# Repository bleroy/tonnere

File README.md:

## Project Tonnere

The EclaireXL was a partially open Atari XL FPGA implementation designed almost a decade ago. This project is intended to be a fully open community follow up version.

## Status

For now there is only a hardware design from which a physical board has been produced. The design goals of this are described below.

## Memory

3 independent banks of RAM from FPGA

- 512KB 16-bit wide 10ns SRAM (for VBXE)
- 2048KB 16-bit wide 10ns SRAM (primary Atari core)
- 32MB 16-bit wide SDRAM (secondary Atari core etc - for large memory expansions, cartridge emulation etc)

## Video output

- HDMI driven directly by FPGA
- Analog video driven by FPGA (3 pins/channel - ~8-bit/channel resolution) filtered/buffered by THS7316.
- NTSC in 480i or 480p, PAL in 576i or 576p
- Polyphasic and area-based scaler allowing 720p, 1080i etc

## Audio output

- PCM5102A DAC

## Audio input

- 12-bit ADC for PBI, SIO, 3.5mm left/right on STM microcontroller

## Joystick ports 1-4

- Directly connected to FPGA (via level shifters)
- Paddle support using STM ADC inputs

## Six USB ports

- 1 USB A internal for keyboard
- 3 USB A external for joystick, keyboard etc
- 1 USB C for power only (next to power switch)
- 1 rear USB C for STM32 DFU (to program it), or to be a mass-storage slave to a PC to copy data on.

## Atari peripheral emulator (ESP32 microcontroller/almost Fujinet)

- Wifi support
- Serial connection to STM32
- SPI master to FPGA (for DMA to RAM, faster than serial via STM)
- SIO pins (all)
- Audio out DAC goes to SIO audio in
- Slave to STM32
- Slave to Atari via SIO
- JTAG for debugging

## Firmware/control (STM32)

- SPI master to FPGA SPI flash chip (to program)
- Can restart FPGA
- SRAM port connected to FPGA (for DMA to Atari core RAM + RAM banks)
- IRQ from FPGA
- 4-bit external SD card interface
- SPI to internal micro SD card (will appear as IDE hard drive to Atari core)
- ADC for sampling (see audio in)
- Serial connection for communication for Atari peripheral emulator
- USB port + stack
- DFU mode for programming, can then program FPGA flash and ESP32 via serial (+BOOT etc).
- HDMI i2c link (to get mode support)
- PLL i2c link (6 programmable clocks for FPGA)
- SWD port for debugging
- UART port for debugging/expansion
- Will run menus etc, via DMA to Atari core (+ potentially framebuffer)

## Atari core (Cyclone 10 LP FPGA)

- Core Atari XL and Atari 800 support
- 2x/4x colour clock Antic/GTIA support
- VBXE
- PokeyMAX
- HDD via IDE emulation on microsd
- Turbo freezer
- Common cartridge banking logic (on RAM)

## Atari ports

- Left cartridge
- PBI with standard extensions (enabled/selected via jumper), 50 pin edge and 50 pin header option.
- SIO (with motor control, without 12V)
- Start/select/option/reset switch headers
- 4 joystick ports

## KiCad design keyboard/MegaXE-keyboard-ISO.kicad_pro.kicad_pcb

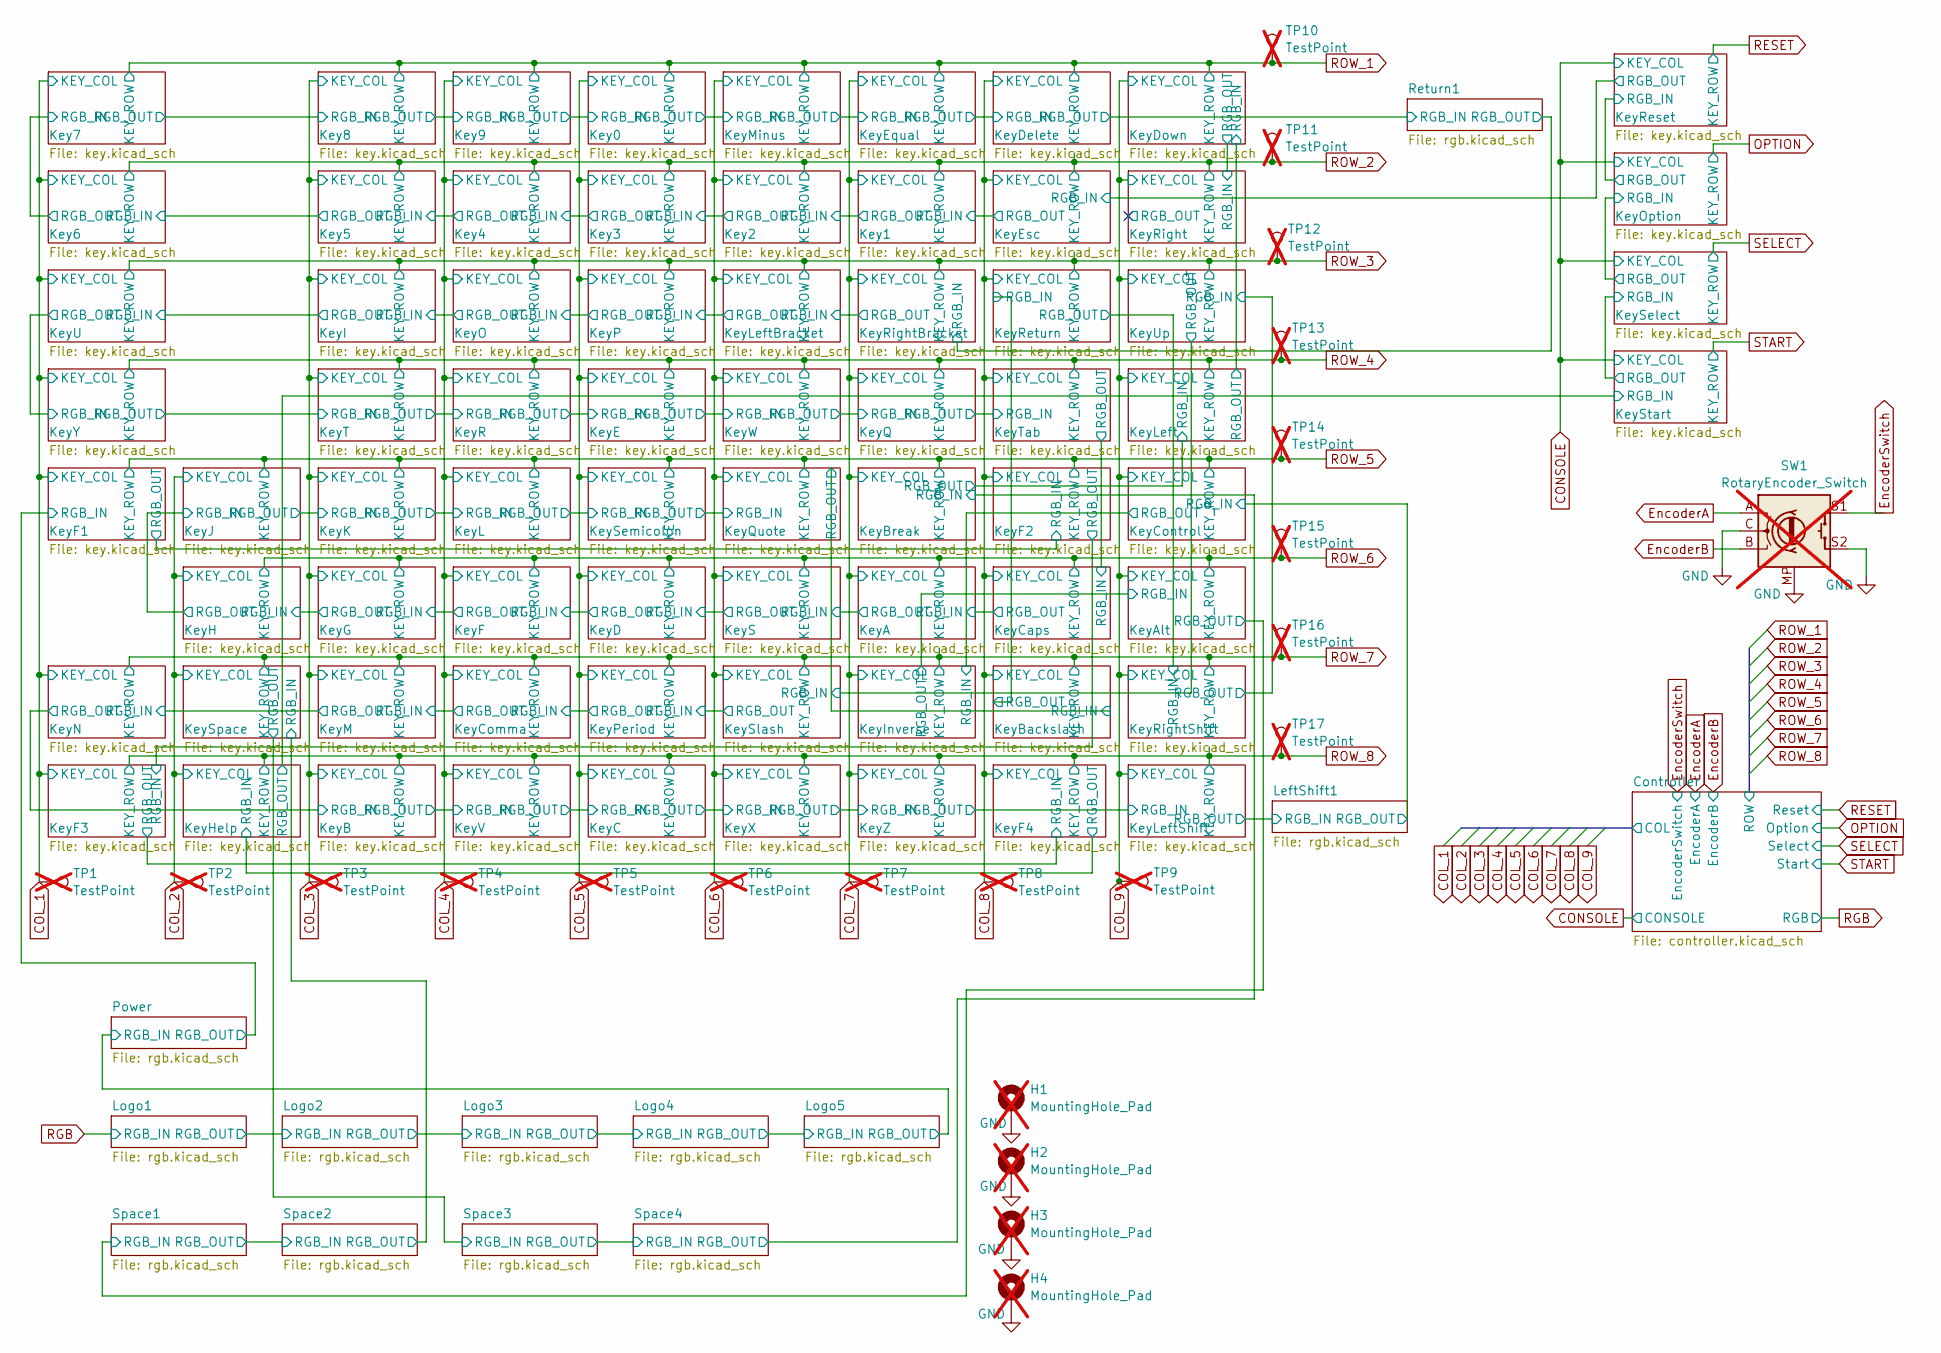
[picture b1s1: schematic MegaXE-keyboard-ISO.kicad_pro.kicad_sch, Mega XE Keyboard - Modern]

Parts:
H1, H2, H3, H4: MountingHole_Pad; MountingHole_2.2mm_M2_Pad_Via; not fitted
SW1: RotaryEncoder_Switch; RotaryEncoder_Alps_EC11E-Switch_Vertical_H20mm; LCSC Part # C470748; not fitted
TP1, TP2, TP3, TP4, TP5, TP6, TP7, TP8, TP9, TP10, TP11, TP12, TP13, TP14, TP15, TP16, TP17: TestPoint; TestPoint_THTPad_D1.0mm_Drill0.5mm; not fitted

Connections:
COL_1: TP1.1 (1_1); also elsewhere on the board
COL_2: TP2.1 (1_1); also elsewhere on the board
COL_3: TP3.1 (1_1); also elsewhere on the board
COL_4: TP4.1 (1_1); also elsewhere on the board
COL_5: TP5.1 (1_1); also elsewhere on the board
COL_6: TP6.1 (1_1); also elsewhere on the board
COL_7: TP7.1 (1_1); also elsewhere on the board
COL_8: TP8.1 (1_1); also elsewhere on the board
COL_9: TP9.1 (1_1); also elsewhere on the board
EncoderA: SW1.A; also elsewhere on the board
EncoderB: SW1.B; also elsewhere on the board
EncoderSwitch: SW1.S1; also elsewhere on the board
GND: H1.1 (1_1), H2.1 (1_1), H3.1 (1_1), H4.1 (1_1), SW1.C, SW1.MP, SW1.S2; also elsewhere on the board
ROW_1: TP10.1 (1_1); also elsewhere on the board
ROW_2: TP11.1 (1_1); also elsewhere on the board
ROW_3: TP12.1 (1_1); also elsewhere on the board
ROW_4: TP13.1 (1_1); also elsewhere on the board
ROW_5: TP14.1 (1_1); also elsewhere on the board
ROW_6: TP15.1 (1_1); also elsewhere on the board
ROW_7: TP16.1 (1_1); also elsewhere on the board
ROW_8: TP17.1 (1_1); also elsewhere on the board

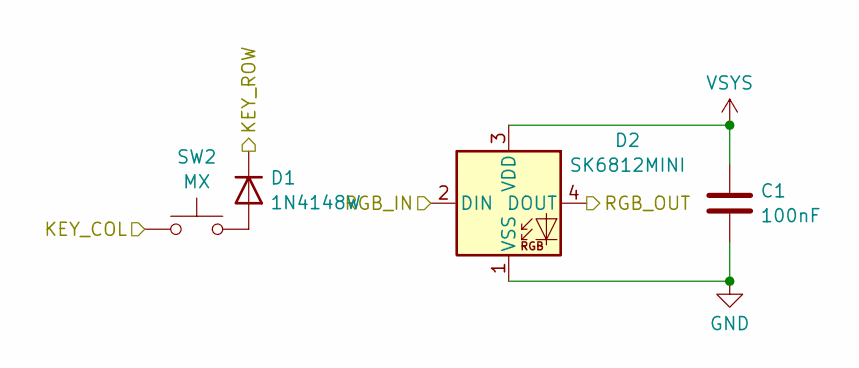
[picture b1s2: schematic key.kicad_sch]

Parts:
C1: 100nF; C_0402_1005Metric; JLCPCB Part # C1525
D1: 1N4148W; D_SOD-123; JLCPCB Part # C81598
D2: SK6812MINI; LED_SK6812MINI-E_3.2x2.8mm_P1.5mm_ReverseMount; JLCPCB Part # C5378731
SW2: MX; Kailh_socket_MX_1-00U; JLCPCB Part # C41430893

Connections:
/Key6/RGB_OUT: D2.2 (DIN); also elsewhere on the board
/Key7/RGB_OUT: D2.4 (DOUT); also elsewhere on the board
COL_1: SW2.1; also elsewhere on the board
GND: C1.2, D2.1 (VSS); also elsewhere on the board
unnamed: D1.2 (A), SW2.2
ROW_1: D1.1 (K); also elsewhere on the board
VSYS: C1.1, D2.3 (VDD); also elsewhere on the board

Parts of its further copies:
C2, C3, C4, C5, C6, C7, C8, C9, C10, C11, C12, C13, C14, C15, C16, C17, C18, C19, C20, C21, C22, C23, C24, C25, C26, C27, C28, C29, C30, C31, C32, C33, C34, C35, C36, C37, C38, C39, C40, C41, C42, C43, C44, C45, C46, C47, C48, C49, C50, C51, C52, C53, C54, C55, C56, C57, C58, C59, C60, C61, C62, C63, C64, C65, C66, C95, C96, C97, C98, C99: 100nF; C_0402_1005Metric; JLCPCB Part # C1525
D3, D5, D7, D9, D11, D13, D15, D17, D19, D21, D23, D25, D27, D29, D31, D33, D35, D37, D39, D41, D43, D45, D47, D49, D51, D53, D55, D57, D59, D61, D63, D65, D67, D69, D71, D73, D75, D77, D79, D81, D83, D85, D87, D89, D91, D93, D95, D97, D99, D101, D103, D105, D107, D109, D111, D113, D115, D117, D119, D121, D123, D125, D127, D129, D131, D144, D146, D148, D150, D152: 1N4148W; D_SOD-123; JLCPCB Part # C81598
D4, D6, D8, D10, D12, D14, D16, D18, D20, D22, D24, D26, D28, D30, D32, D34, D36, D38, D40, D42, D44, D46, D48, D50, D52, D54, D56, D58, D60, D62, D64, D66, D68, D70, D72, D74, D76, D78, D80, D82, D84, D86, D88, D90, D92, D94, D96, D98, D100, D102, D104, D106, D108, D110, D112, D114, D116, D118, D120, D122, D124, D126, D128, D130, D132, D145, D147, D149, D151, D153: SK6812MINI; LED_SK6812MINI-E_3.2x2.8mm_P1.5mm_ReverseMount; JLCPCB Part # C5378731
SW3, SW4, SW5, SW6, SW7, SW8, SW9, SW10, SW11, SW12, SW13, SW14, SW15, SW16, SW17, SW18, SW19, SW20, SW21, SW22, SW23, SW24, SW25, SW26, SW27, SW28, SW29, SW30, SW31, SW32, SW33, SW34, SW35, SW36, SW37, SW38, SW39, SW40, SW41, SW42, SW43, SW44, SW45, SW46, SW47, SW48, SW49, SW50, SW51, SW52, SW53, SW54, SW55, SW56, SW57, SW58, SW59, SW60, SW61, SW62, SW63, SW64, SW65, SW66, SW67, SW70, SW71, SW72, SW73, SW74: MX; Kailh_socket_MX_1-00U; JLCPCB Part # C41430893

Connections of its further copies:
/Key0/RGB_IN: D40.4 (DOUT), D58.2 (DIN)
/Key0/RGB_OUT: D58.4 (DOUT), D72.2 (DIN)
/Key1/RGB_IN: D88.2 (DIN), D104.4 (DOUT)
/Key1/RGB_OUT: D74.2 (DIN), D88.4 (DOUT)
/Key2/RGB_OUT: D56.2 (DIN), D74.4 (DOUT)
/Key3/RGB_OUT: D42.2 (DIN), D56.4 (DOUT)
/Key4/RGB_OUT: D36.2 (DIN), D42.4 (DOUT)
/Key5/RGB_OUT: D4.2 (DIN), D36.4 (DOUT)
/Key6/RGB_OUT: D4.4 (DOUT); also elsewhere on the board
/Key7/RGB_OUT: D38.2 (DIN); also elsewhere on the board
/Key8/RGB_OUT: D38.4 (DOUT), D40.2 (DIN)
/KeyA/RGB_IN: D96.2 (DIN), D106.4 (DOUT)
/KeyA/RGB_OUT: D78.2 (DIN), D96.4 (DOUT)
/KeyAlt/RGB_IN: D98.4 (DOUT), D149.2 (DIN)
/KeyAlt/RGB_OUT: D149.4 (DOUT); also elsewhere on the board
/KeyB/RGB_IN: D12.4 (DOUT), D24.2 (DIN)
/KeyB/RGB_OUT: D24.4 (DOUT), D54.2 (DIN)
/KeyBackslash/RGB_IN: D86.4 (DOUT), D153.2 (DIN)
/KeyBackslash/RGB_OUT: D108.2 (DIN), D153.4 (DOUT)
/KeyBreak/RGB_IN: D151.2 (DIN); also elsewhere on the board
/KeyBreak/RGB_OUT: D147.2 (DIN), D151.4 (DOUT)
/KeyC/RGB_IN: D54.4 (DOUT), D70.2 (DIN)
/KeyC/RGB_OUT: D70.4 (DOUT), D76.2 (DIN)
/KeyCaps/RGB_IN: D106.2 (DIN), D114.4 (DOUT)
/KeyComma/RGB_IN: D52.2 (DIN), D60.4 (DOUT)
/KeyComma/RGB_OUT: D26.2 (DIN), D52.4 (DOUT)
/KeyControl/RGB_IN: D112.2 (DIN); also elsewhere on the board
/KeyControl/RGB_OUT: D98.2 (DIN), D112.4 (DOUT)
/KeyD/RGB_IN: D64.2 (DIN), D78.4 (DOUT)
/KeyD/RGB_OUT: D50.2 (DIN), D64.4 (DOUT)
/KeyDelete/RGB_IN: D92.4 (DOUT), D110.2 (DIN)
/KeyDelete/RGB_OUT: D110.4 (DOUT); also elsewhere on the board
/KeyDown/RGB_IN: D122.2 (DIN), D147.4 (DOUT)
/KeyDown/RGB_OUT: D122.4 (DOUT), D145.2 (DIN)
/KeyE/RGB_IN: D46.4 (DOUT), D68.2 (DIN)
/KeyE/RGB_OUT: D68.4 (DOUT), D80.2 (DIN)
/KeyEqual/RGB_IN: D72.4 (DOUT), D92.2 (DIN)
/KeyEsc/RGB_IN: D104.2 (DIN), D124.4 (DOUT)
/KeyF1/RGB_IN: D10.2 (DIN); also elsewhere on the board
/KeyF1/RGB_OUT: D10.4 (DOUT), D116.2 (DIN)
/KeyF2/RGB_OUT: D20.2 (DIN), D116.4 (DOUT)
/KeyF3/RGB_OUT: D20.4 (DOUT), D118.2 (DIN)
/KeyF4/RGB_OUT: D22.2 (DIN), D118.4 (DOUT)
/KeyF/RGB_OUT: D28.2 (DIN), D50.4 (DOUT)
/KeyG/RGB_OUT: D16.2 (DIN), D28.4 (DOUT)
/KeyH/RGB_OUT: D14.2 (DIN), D16.4 (DOUT)
/KeyHelp/RGB_OUT: D22.4 (DOUT), D130.2 (DIN)
/KeyI/RGB_IN: D34.2 (DIN), D44.4 (DOUT)
/KeyI/RGB_OUT: D6.2 (DIN), D34.4 (DOUT)
/KeyJ/RGB_OUT: D14.4 (DOUT), D30.2 (DIN)
/KeyK/RGB_OUT: D30.4 (DOUT), D48.2 (DIN)
/KeyL/RGB_OUT: D48.4 (DOUT), D66.2 (DIN)
/KeyLeftBracket/RGB_IN: D82.2 (DIN), D90.4 (DOUT)
/KeyLeftBracket/RGB_OUT: D62.2 (DIN), D82.4 (DOUT)
/KeyLeftShift/RGB_IN: D102.4 (DOUT), D120.2 (DIN)
/KeyLeftShift/RGB_OUT: D120.4 (DOUT); also elsewhere on the board
/KeyM/RGB_OUT: D12.2 (DIN), D26.4 (DOUT)
/KeyO/RGB_IN: D44.2 (DIN), D62.4 (DOUT)
/KeyOption/RGB_IN: D126.2 (DIN), D128.4 (DOUT)
/KeyOption/RGB_OUT: D124.2 (DIN), D126.4 (DOUT)
/KeyPeriod/RGB_IN: D60.2 (DIN), D84.4 (DOUT)
/KeyQ/RGB_IN: D80.4 (DOUT), D100.2 (DIN)
/KeyQ/RGB_OUT: D100.4 (DOUT), D114.2 (DIN)
/KeyQuote/RGB_IN: D66.4 (DOUT), D86.2 (DIN)
/KeyR/RGB_IN: D32.4 (DOUT), D46.2 (DIN)
/KeyReturn/RGB_OUT: D108.4 (DOUT), D132.2 (DIN)
/KeyRight/RGB_OUT: D145.4 (DOUT)
/KeyRightBracket/RGB_IN: D90.2 (DIN); also elsewhere on the board
/KeyRightShift/RGB_OUT: D94.2 (DIN), D132.4 (DOUT)
/KeySelect/RGB_IN: D128.2 (DIN), D130.4 (DOUT)
/KeySlash/RGB_IN: D84.2 (DIN), D94.4 (DOUT)
/KeySpace/RGB_IN: D18.2 (DIN); also elsewhere on the board
/KeySpace/RGB_OUT: D18.4 (DOUT); also elsewhere on the board
/KeyT/RGB_IN: D8.4 (DOUT), D32.2 (DIN)
/KeyU/RGB_OUT: D6.4 (DOUT), D8.2 (DIN)
/KeyX/RGB_OUT: D76.4 (DOUT), D102.2 (DIN)
COL_1: SW3.1, SW4.1, SW5.1, SW6.1, SW7.1, SW11.1; also elsewhere on the board
COL_2: SW8.1, SW9.1, SW10.1, SW12.1; also elsewhere on the board
COL_3: SW13.1, SW14.1, SW15.1, SW16.1, SW17.1, SW18.1, SW19.1, SW20.1; also elsewhere on the board
COL_4: SW21.1, SW22.1, SW23.1, SW24.1, SW25.1, SW26.1, SW27.1, SW28.1; also elsewhere on the board
COL_5: SW29.1, SW30.1, SW31.1, SW32.1, SW33.1, SW34.1, SW35.1, SW36.1; also elsewhere on the board
COL_6: SW37.1, SW38.1, SW39.1, SW40.1, SW41.1, SW42.1, SW43.1, SW44.1; also elsewhere on the board
COL_7: SW45.1, SW46.1, SW47.1, SW49.1, SW50.1, SW51.1, SW52.1, SW73.1; also elsewhere on the board
COL_8: SW53.1, SW54.1, SW55.1, SW56.1, SW58.1, SW59.1, SW60.1, SW74.1; also elsewhere on the board
COL_9: SW48.1, SW57.1, SW61.1, SW62.1, SW67.1, SW70.1, SW71.1, SW72.1; also elsewhere on the board
CONSOLE: SW63.1, SW64.1, SW65.1, SW66.1; also elsewhere on the board
GND: C2.2, C3.2, C4.2, C5.2, C6.2, C7.2, C8.2, C9.2, C10.2, C11.2, C12.2, C13.2, C14.2, C15.2, C16.2, C17.2, C18.2, C19.2, C20.2, C21.2, C22.2, C23.2, C24.2, C25.2, C26.2, C27.2, C28.2, C29.2, C30.2, C31.2, C32.2, C33.2, C34.2, C35.2, C36.2, C37.2, C38.2, C39.2, C40.2, C41.2, C42.2, C43.2, C44.2, C45.2, C46.2, C47.2, C48.2, C49.2, C50.2, C51.2, C52.2, C53.2, C54.2, C55.2, C56.2, C57.2, C58.2, C59.2, C60.2, C61.2, C62.2, C63.2, C64.2, C65.2, C66.2, C95.2, C96.2, C97.2, C98.2, C99.2, D4.1 (VSS), D6.1 (VSS), D8.1 (VSS), D10.1 (VSS), D12.1 (VSS), D14.1 (VSS), D16.1 (VSS), D18.1 (VSS), D20.1 (VSS), D22.1 (VSS), D24.1 (VSS), D26.1 (VSS), D28.1 (VSS), D30.1 (VSS), D32.1 (VSS), D34.1 (VSS), D36.1 (VSS), D38.1 (VSS), D40.1 (VSS), D42.1 (VSS), D44.1 (VSS), D46.1 (VSS), D48.1 (VSS), D50.1 (VSS), D52.1 (VSS), D54.1 (VSS), D56.1 (VSS), D58.1 (VSS), D60.1 (VSS), D62.1 (VSS), D64.1 (VSS), D66.1 (VSS), D68.1 (VSS), D70.1 (VSS), D72.1 (VSS), D74.1 (VSS), D76.1 (VSS), D78.1 (VSS), D80.1 (VSS), D82.1 (VSS), D84.1 (VSS), D86.1 (VSS), D88.1 (VSS), D90.1 (VSS), D92.1 (VSS), D94.1 (VSS), D96.1 (VSS), D98.1 (VSS), D100.1 (VSS), D102.1 (VSS), D104.1 (VSS), D106.1 (VSS), D108.1 (VSS), D110.1 (VSS), D112.1 (VSS), D114.1 (VSS), D116.1 (VSS), D118.1 (VSS), D120.1 (VSS), D122.1 (VSS), D124.1 (VSS), D126.1 (VSS), D128.1 (VSS), D130.1 (VSS), D132.1 (VSS), D145.1 (VSS), D147.1 (VSS), D149.1 (VSS), D151.1 (VSS), D153.1 (VSS); also elsewhere on the board
unnamed: D3.2 (A), SW3.2
unnamed: D5.2 (A), SW4.2
unnamed: D7.2 (A), SW5.2
unnamed: D9.2 (A), SW6.2
unnamed: D11.2 (A), SW7.2
unnamed: D13.2 (A), SW8.2
unnamed: D15.2 (A), SW9.2
unnamed: D17.2 (A), SW10.2
unnamed: D19.2 (A), SW11.2
unnamed: D21.2 (A), SW12.2
unnamed: D23.2 (A), SW13.2
unnamed: D25.2 (A), SW14.2
unnamed: D27.2 (A), SW15.2
unnamed: D29.2 (A), SW16.2
unnamed: D31.2 (A), SW17.2
unnamed: D33.2 (A), SW18.2
unnamed: D35.2 (A), SW19.2
unnamed: D37.2 (A), SW20.2
unnamed: D39.2 (A), SW21.2
unnamed: D41.2 (A), SW22.2
unnamed: D43.2 (A), SW23.2
unnamed: D45.2 (A), SW24.2
unnamed: D47.2 (A), SW25.2
unnamed: D49.2 (A), SW26.2
unnamed: D51.2 (A), SW27.2
unnamed: D53.2 (A), SW28.2
unnamed: D55.2 (A), SW29.2
unnamed: D57.2 (A), SW30.2
unnamed: D59.2 (A), SW31.2
unnamed: D61.2 (A), SW32.2
unnamed: D63.2 (A), SW33.2
unnamed: D65.2 (A), SW34.2
unnamed: D67.2 (A), SW35.2
unnamed: D69.2 (A), SW36.2
unnamed: D71.2 (A), SW37.2
unnamed: D73.2 (A), SW38.2
unnamed: D75.2 (A), SW39.2
unnamed: D77.2 (A), SW40.2
unnamed: D79.2 (A), SW41.2
unnamed: D81.2 (A), SW42.2
unnamed: D83.2 (A), SW43.2
unnamed: D85.2 (A), SW44.2
unnamed: D87.2 (A), SW45.2
unnamed: D89.2 (A), SW46.2
unnamed: D91.2 (A), SW47.2
unnamed: D93.2 (A), SW48.2
unnamed: D95.2 (A), SW49.2
unnamed: D97.2 (A), SW50.2
unnamed: D99.2 (A), SW51.2
unnamed: D101.2 (A), SW52.2
unnamed: D103.2 (A), SW53.2
unnamed: D105.2 (A), SW54.2
unnamed: D107.2 (A), SW55.2
unnamed: D109.2 (A), SW56.2
unnamed: D111.2 (A), SW57.2
unnamed: D113.2 (A), SW58.2
unnamed: D115.2 (A), SW59.2
unnamed: D117.2 (A), SW60.2
unnamed: D119.2 (A), SW61.2
unnamed: D121.2 (A), SW62.2
unnamed: D123.2 (A), SW63.2
unnamed: D125.2 (A), SW64.2
unnamed: D127.2 (A), SW65.2
unnamed: D129.2 (A), SW66.2
unnamed: D131.2 (A), SW67.2
unnamed: D144.2 (A), SW70.2
unnamed: D146.2 (A), SW71.2
unnamed: D148.2 (A), SW72.2
unnamed: D150.2 (A), SW73.2
unnamed: D152.2 (A), SW74.2
OPTION: D125.1 (K); also elsewhere on the board
RESET: D123.1 (K); also elsewhere on the board
ROW_1: D37.1 (K), D39.1 (K), D57.1 (K), D71.1 (K), D91.1 (K), D109.1 (K), D121.1 (K); also elsewhere on the board
ROW_2: D3.1 (K), D35.1 (K), D41.1 (K), D55.1 (K), D73.1 (K), D87.1 (K), D103.1 (K), D144.1 (K); also elsewhere on the board
ROW_3: D5.1 (K), D33.1 (K), D43.1 (K), D61.1 (K), D81.1 (K), D89.1 (K), D93.1 (K), D107.1 (K); also elsewhere on the board
ROW_4: D7.1 (K), D31.1 (K), D45.1 (K), D67.1 (K), D79.1 (K), D99.1 (K), D113.1 (K), D146.1 (K); also elsewhere on the board
ROW_5: D9.1 (K), D13.1 (K), D29.1 (K), D47.1 (K), D65.1 (K), D85.1 (K), D111.1 (K), D115.1 (K), D150.1 (K); also elsewhere on the board
ROW_6: D15.1 (K), D27.1 (K), D49.1 (K), D63.1 (K), D77.1 (K), D95.1 (K), D105.1 (K), D148.1 (K); also elsewhere on the board
ROW_7: D11.1 (K), D17.1 (K), D25.1 (K), D51.1 (K), D59.1 (K), D83.1 (K), D97.1 (K), D131.1 (K), D152.1 (K); also elsewhere on the board
ROW_8: D19.1 (K), D21.1 (K), D23.1 (K), D53.1 (K), D69.1 (K), D75.1 (K), D101.1 (K), D117.1 (K), D119.1 (K); also elsewhere on the board
SELECT: D127.1 (K); also elsewhere on the board
START: D129.1 (K); also elsewhere on the board
VSYS: C2.1, C3.1, C4.1, C5.1, C6.1, C7.1, C8.1, C9.1, C10.1, C11.1, C12.1, C13.1, C14.1, C15.1, C16.1, C17.1, C18.1, C19.1, C20.1, C21.1, C22.1, C23.1, C24.1, C25.1, C26.1, C27.1, C28.1, C29.1, C30.1, C31.1, C32.1, C33.1, C34.1, C35.1, C36.1, C37.1, C38.1, C39.1, C40.1, C41.1, C42.1, C43.1, C44.1, C45.1, C46.1, C47.1, C48.1, C49.1, C50.1, C51.1, C52.1, C53.1, C54.1, C55.1, C56.1, C57.1, C58.1, C59.1, C60.1, C61.1, C62.1, C63.1, C64.1, C65.1, C66.1, C95.1, C96.1, C97.1, C98.1, C99.1, D4.3 (VDD), D6.3 (VDD), D8.3 (VDD), D10.3 (VDD), D12.3 (VDD), D14.3 (VDD), D16.3 (VDD), D18.3 (VDD), D20.3 (VDD), D22.3 (VDD), D24.3 (VDD), D26.3 (VDD), D28.3 (VDD), D30.3 (VDD), D32.3 (VDD), D34.3 (VDD), D36.3 (VDD), D38.3 (VDD), D40.3 (VDD), D42.3 (VDD), D44.3 (VDD), D46.3 (VDD), D48.3 (VDD), D50.3 (VDD), D52.3 (VDD), D54.3 (VDD), D56.3 (VDD), D58.3 (VDD), D60.3 (VDD), D62.3 (VDD), D64.3 (VDD), D66.3 (VDD), D68.3 (VDD), D70.3 (VDD), D72.3 (VDD), D74.3 (VDD), D76.3 (VDD), D78.3 (VDD), D80.3 (VDD), D82.3 (VDD), D84.3 (VDD), D86.3 (VDD), D88.3 (VDD), D90.3 (VDD), D92.3 (VDD), D94.3 (VDD), D96.3 (VDD), D98.3 (VDD), D100.3 (VDD), D102.3 (VDD), D104.3 (VDD), D106.3 (VDD), D108.3 (VDD), D110.3 (VDD), D112.3 (VDD), D114.3 (VDD), D116.3 (VDD), D118.3 (VDD), D120.3 (VDD), D122.3 (VDD), D124.3 (VDD), D126.3 (VDD), D128.3 (VDD), D130.3 (VDD), D132.3 (VDD), D145.3 (VDD), D147.3 (VDD), D149.3 (VDD), D151.3 (VDD), D153.3 (VDD); also elsewhere on the board

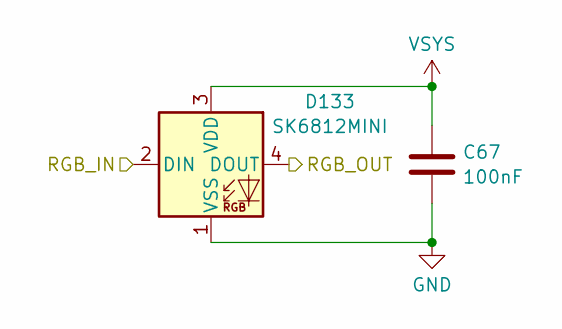
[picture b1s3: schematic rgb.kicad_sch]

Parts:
C67: 100nF; C_0402_1005Metric; LCSC Part # C1525
D133: SK6812MINI; LED_SK6812MINI-E_3.2x2.8mm_P1.5mm_ReverseMount; LCSC Part # C5378731

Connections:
/KeyF1/RGB_IN: D133.4 (DOUT); also elsewhere on the board
/Logo5/RGB_OUT: D133.2 (DIN); also elsewhere on the board
GND: C67.2, D133.1 (VSS); also elsewhere on the board
VSYS: C67.1, D133.3 (VDD); also elsewhere on the board

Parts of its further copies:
C68, C69, C70, C71, C72, C73, C74, C75, C76, C77, C100: 100nF; C_0402_1005Metric; LCSC Part # C1525
D134, D135, D136, D137, D138, D139, D140, D141, D142, D143, D154: SK6812MINI; LED_SK6812MINI-E_3.2x2.8mm_P1.5mm_ReverseMount; LCSC Part # C5378731

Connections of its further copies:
/KeyAlt/RGB_OUT: D140.2 (DIN); also elsewhere on the board
/KeyBreak/RGB_IN: D143.4 (DOUT); also elsewhere on the board
/KeyControl/RGB_IN: D154.4 (DOUT); also elsewhere on the board
/KeyDelete/RGB_OUT: D134.2 (DIN); also elsewhere on the board
/KeyLeftShift/RGB_OUT: D154.2 (DIN); also elsewhere on the board
/KeyRightBracket/RGB_IN: D134.4 (DOUT); also elsewhere on the board
/KeySpace/RGB_IN: D141.4 (DOUT); also elsewhere on the board
/KeySpace/RGB_OUT: D142.2 (DIN); also elsewhere on the board
/Logo1/RGB_OUT: D135.4 (DOUT), D136.2 (DIN)
/Logo2/RGB_OUT: D136.4 (DOUT), D137.2 (DIN)
/Logo3/RGB_OUT: D137.4 (DOUT), D138.2 (DIN)
/Logo4/RGB_OUT: D138.4 (DOUT), D139.2 (DIN)
/Logo5/RGB_OUT: D139.4 (DOUT); also elsewhere on the board
/Space1/RGB_OUT: D140.4 (DOUT), D141.2 (DIN)
/Space3/RGB_OUT: D142.4 (DOUT), D143.2 (DIN)
GND: C68.2, C69.2, C70.2, C71.2, C72.2, C73.2, C74.2, C75.2, C76.2, C77.2, C100.2, D134.1 (VSS), D135.1 (VSS), D136.1 (VSS), D137.1 (VSS), D138.1 (VSS), D139.1 (VSS), D140.1 (VSS), D141.1 (VSS), D142.1 (VSS), D143.1 (VSS), D154.1 (VSS); also elsewhere on the board
RGB: D135.2 (DIN); also elsewhere on the board
VSYS: C68.1, C69.1, C70.1, C71.1, C72.1, C73.1, C74.1, C75.1, C76.1, C77.1, C100.1, D134.3 (VDD), D135.3 (VDD), D136.3 (VDD), D137.3 (VDD), D138.3 (VDD), D139.3 (VDD), D140.3 (VDD), D141.3 (VDD), D142.3 (VDD), D143.3 (VDD), D154.3 (VDD); also elsewhere on the board

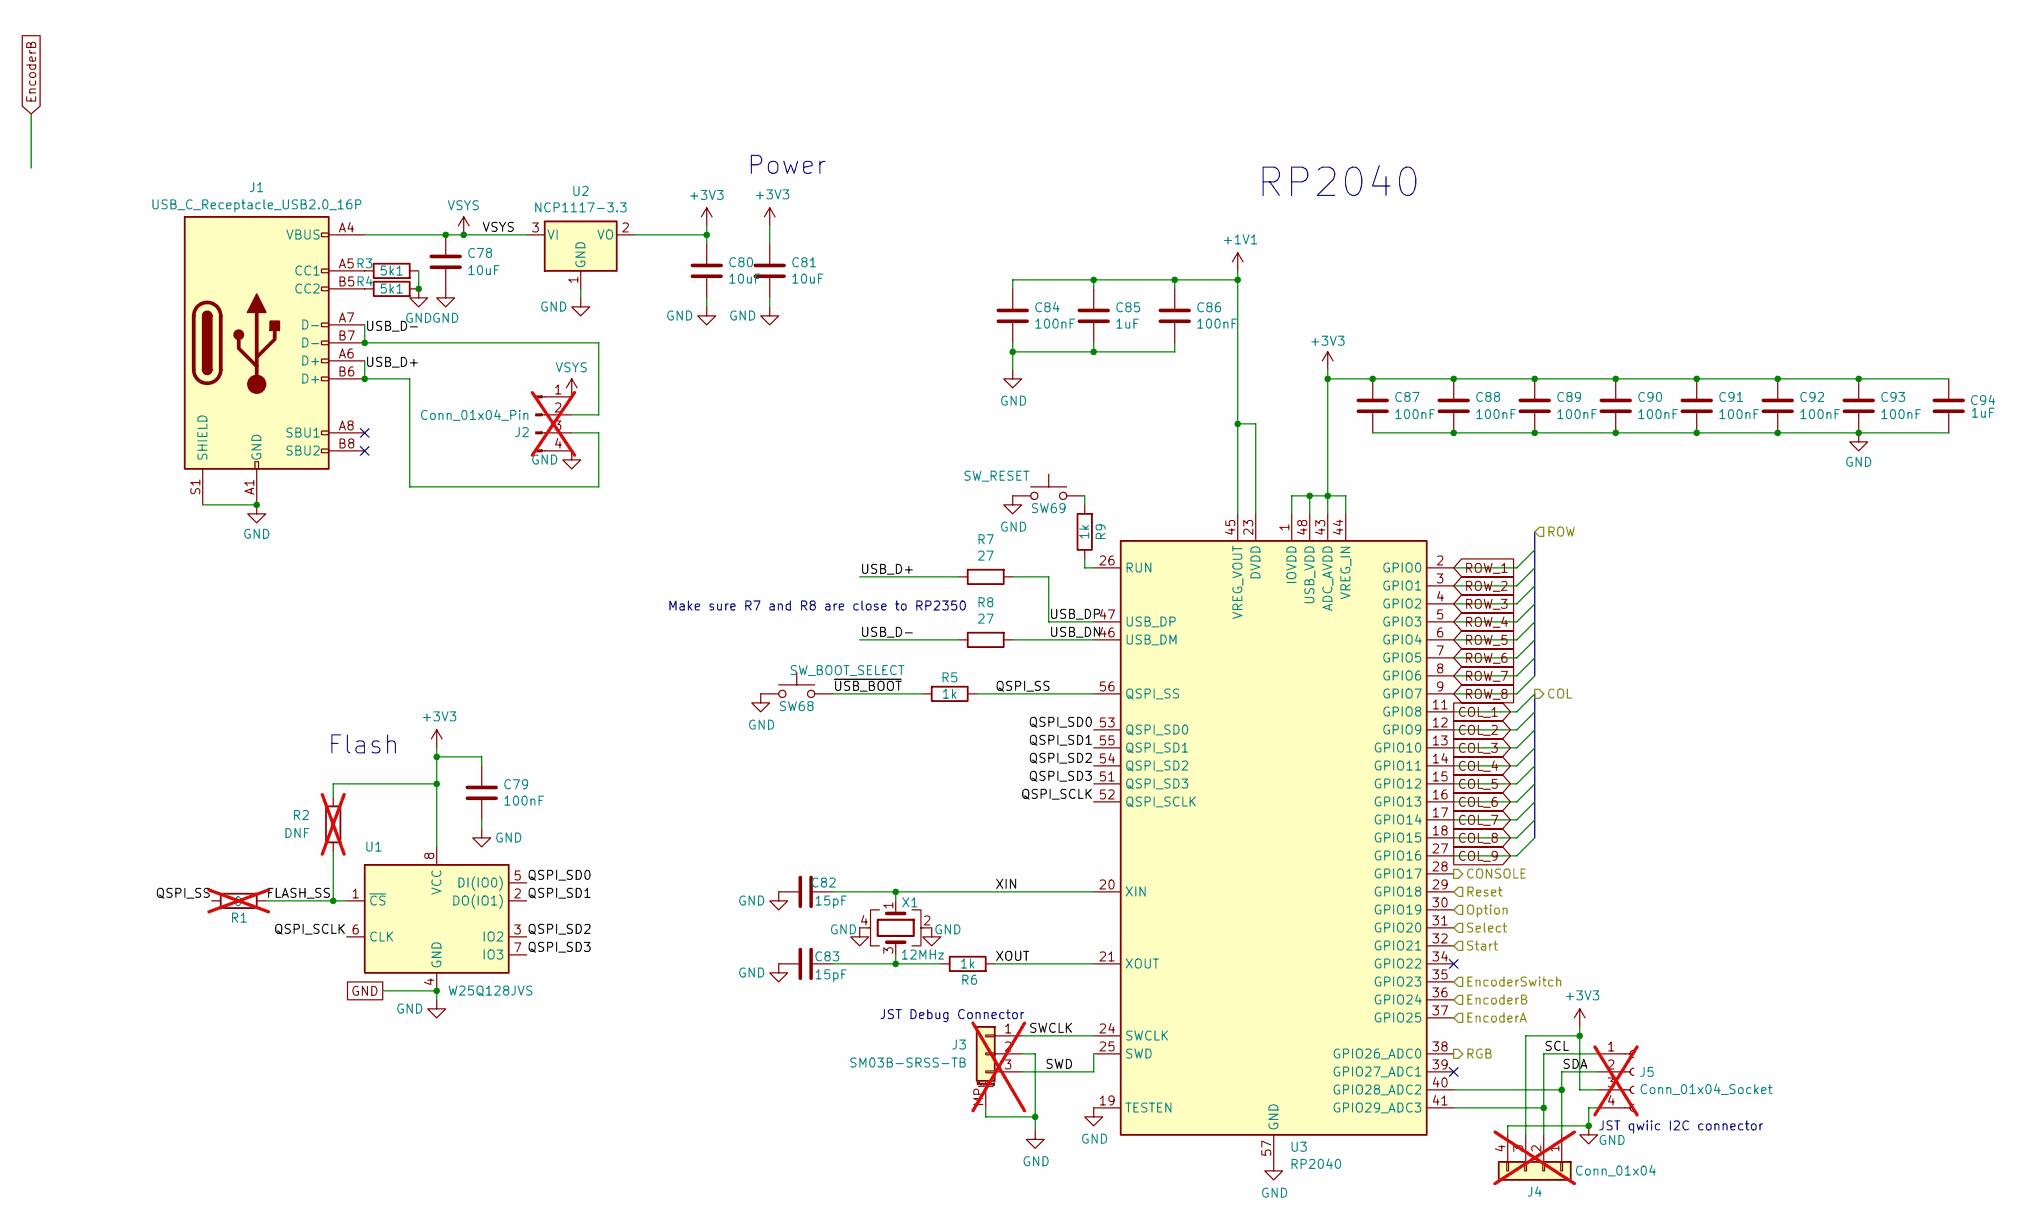
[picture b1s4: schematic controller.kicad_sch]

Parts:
C78, C80, C81: 10uF; C_0402_1005Metric; LCSC Part # C15525
C79, C84, C86, C87, C88, C89, C90, C91, C92, C93: 100nF; C_0402_1005Metric; LCSC Part # C1525
C82, C83: 15pF; C_0402_1005Metric; LCSC Part # C1548
C85, C94: 1uF; C_0402_1005Metric; LCSC Part # C52923
J1: USB_C_Receptacle_USB2.0_16P; USB_C_Receptacle_C2765186; LCSC Part # C2765186
J2: Conn_01x04_Pin; PinHeader_1x04_P2.54mm_Vertical; not fitted
J3: SM03B-SRSS-TB; JST_SH_BM03B-SRSS-TB_1x03-1MP_P1.00mm_Vertical; LCSC Part # C160389; not fitted
J4: Conn_01x04; PinHeader_1x04_P2.54mm_Vertical; not fitted
J5: Conn_01x04_Socket; JST_PH_B4B-PH-K_1x04_P2.00mm_Vertical; LCSC Part # C131334; not fitted
R1: 0; SolderJumper-2_P1.3mm_Bridged_RoundedPad1.0x1.5mm; not fitted
R2: DNF; R_0402_1005Metric; not fitted
R3, R4: 5k1; R_0402_1005Metric; LCSC Part # C25905
R5, R6, R9: 1k; R_0402_1005Metric; LCSC Part # C11702
R7, R8: 27; R_0402_1005Metric; LCSC Part # C138021
SW68: SW_BOOT_SELECT; TactileSwitch; LCSC Part # C720477
SW69: SW_RESET; TactileSwitch; LCSC Part # C720477
U1: W25Q128JVS; SOIC-8_5.3x5.3mm_P1.27mm; LCSC Part # C97521
U2: NCP1117-3.3; SOT-223-3_TabPin2; LCSC Part # C6186
U3: RP2040; QFN-56-1EP_7x7mm_P0.4mm_EP3.2x3.2mm; LCSC Part # C2040
X1: 12MHz; Crystal_SMD_Abracon_ABM8AIG-4Pin_3.2x2.5mm; LCSC Part # C9002

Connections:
+1V1: C84.1, C85.1, C86.1, U3.23 (DVDD), U3.45 (VREG_VOUT), U3.50 (DVDD)
+3V3: C79.1, C80.1, C81.1, C87.1, C88.1, C89.1, C90.1, C91.1, C92.1, C93.1, C94.1, J4.3, J5.3, R2.1, U1.8 (VCC), U2.2 (VO), U3.1 (IOVDD), U3.10 (IOVDD), U3.22 (IOVDD), U3.33 (IOVDD), U3.42 (IOVDD), U3.43 (ADC_AVDD), U3.44 (VREG_IN), U3.48 (USB_VDD), U3.49 (IOVDD)
/Controller/FLASH_SS: R1.2, R2.2, U1.1 (~CS)
/Controller/QSPI_SCLK: U1.6 (CLK), U3.52 (QSPI_SCLK)
/Controller/QSPI_SD0: U1.5 (DI(IO0)), U3.53 (QSPI_SD0)
/Controller/QSPI_SD1: U1.2 (DO(IO1)), U3.55 (QSPI_SD1)
/Controller/QSPI_SD2: U1.3 (IO2), U3.54 (QSPI_SD2)
/Controller/QSPI_SD3: U1.7 (IO3), U3.51 (QSPI_SD3)
/Controller/QSPI_SS: R1.1, R5.1, U3.56 (QSPI_SS)
/Controller/SCL: J4.2, J5.1, U3.41 (GPIO29_ADC3)
/Controller/SDA: J4.1, J5.2, U3.40 (GPIO28_ADC2)
/Controller/SWCLK: J3.1, U3.24 (SWCLK)
/Controller/SWD: J3.3, U3.25 (SWD)
/Controller/USB_D+: J1.A6 (D+), J1.B6 (D+), J2.3, R7.1
/Controller/USB_D-: J1.A7 (D-), J1.B7 (D-), J2.2, R8.1
/Controller/USB_DN: R8.2, U3.46 (USB_DM)
/Controller/USB_DP: R7.2, U3.47 (USB_DP)
/Controller/XIN: C82.1, U3.20 (XIN), X1.1
/Controller/XOUT: R6.2, U3.21 (XOUT)
/Controller/~USB_BOOT: R5.2, SW68.2
COL_1: U3.11 (GPIO8); also elsewhere on the board
COL_2: U3.12 (GPIO9); also elsewhere on the board
COL_3: U3.13 (GPIO10); also elsewhere on the board
COL_4: U3.14 (GPIO11); also elsewhere on the board
COL_5: U3.15 (GPIO12); also elsewhere on the board
COL_6: U3.16 (GPIO13); also elsewhere on the board
COL_7: U3.17 (GPIO14); also elsewhere on the board
COL_8: U3.18 (GPIO15); also elsewhere on the board
COL_9: U3.27 (GPIO16); also elsewhere on the board
CONSOLE: U3.28 (GPIO17); also elsewhere on the board
EncoderA: U3.37 (GPIO25); also elsewhere on the board
EncoderB: U3.36 (GPIO24); also elsewhere on the board
EncoderSwitch: U3.35 (GPIO23); also elsewhere on the board
GND: C78.1, C79.2, C80.2, C81.2, C82.2, C83.1, C84.2, C85.2, C86.2, C87.2, C88.2, C89.2, C90.2, C91.2, C92.2, C93.2, C94.2, J1.A1 (GND), J1.A12 (GND), J1.B1 (GND), J1.B12 (GND), J1.S1 (SHIELD), J2.4, J3.2, J3.MP (MountPin), J4.4, J5.4, R3.2, R4.2, SW68.1, SW69.1, U1.4 (GND), U2.1 (GND), U3.19 (TESTEN), U3.57 (GND), X1.2, X1.4; also elsewhere on the board
unnamed: C83.2, R6.1, X1.3
unnamed: J1.A5 (CC1), R3.1
unnamed: J1.B5 (CC2), R4.1
unnamed: R9.2, SW69.2
unnamed: R9.1, U3.26 (RUN)
OPTION: U3.30 (GPIO19); also elsewhere on the board
RESET: U3.29 (GPIO18); also elsewhere on the board
RGB: U3.38 (GPIO26_ADC0); also elsewhere on the board
ROW_1: U3.2 (GPIO0); also elsewhere on the board
ROW_2: U3.3 (GPIO1); also elsewhere on the board
ROW_3: U3.4 (GPIO2); also elsewhere on the board
ROW_4: U3.5 (GPIO3); also elsewhere on the board
ROW_5: U3.6 (GPIO4); also elsewhere on the board
ROW_6: U3.7 (GPIO5); also elsewhere on the board
ROW_7: U3.8 (GPIO6); also elsewhere on the board
ROW_8: U3.9 (GPIO7); also elsewhere on the board
SELECT: U3.31 (GPIO20); also elsewhere on the board
START: U3.32 (GPIO21); also elsewhere on the board
VSYS: C78.2, J1.A4 (VBUS), J1.A9 (VBUS), J1.B4 (VBUS), J1.B9 (VBUS), J2.1, U2.3 (VI); also elsewhere on the board

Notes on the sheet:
Power
RP2040
Make sure R7 and R8 are close to RP2350
Flash
JST qwiic I2C connector
JST Debug Connector

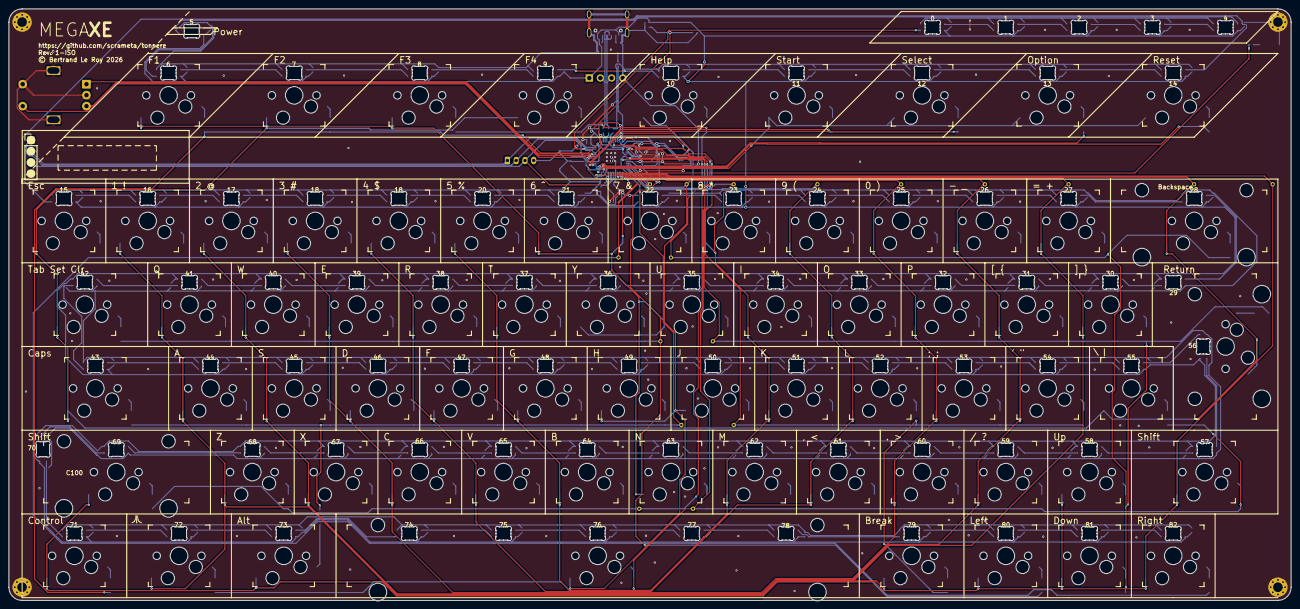
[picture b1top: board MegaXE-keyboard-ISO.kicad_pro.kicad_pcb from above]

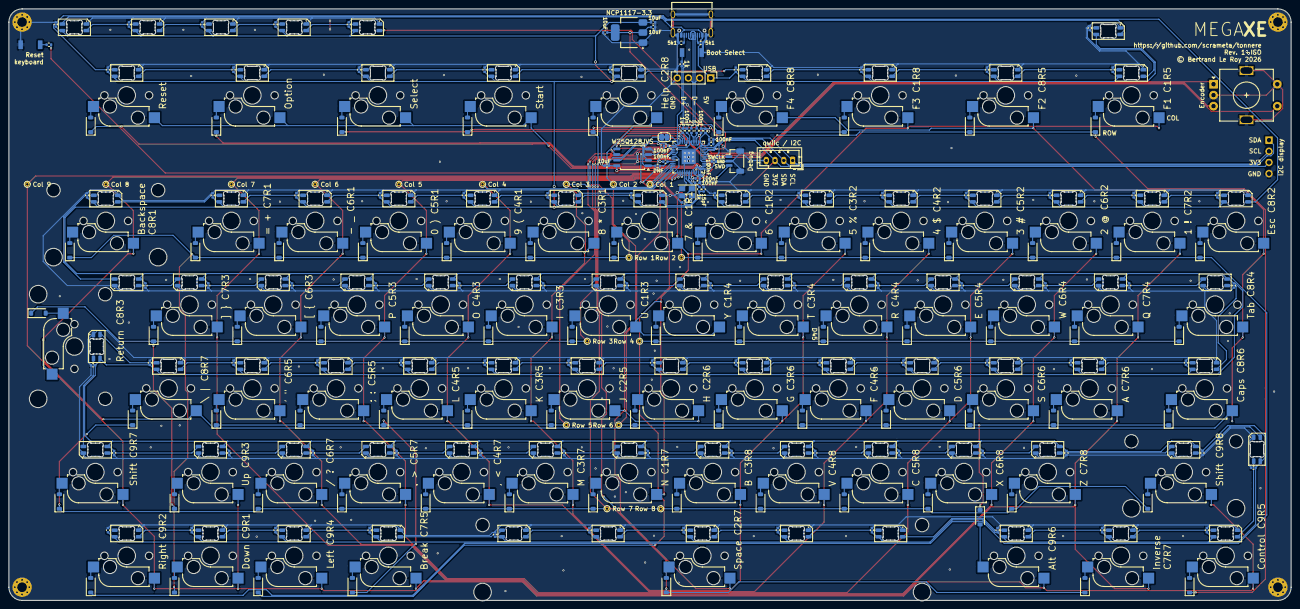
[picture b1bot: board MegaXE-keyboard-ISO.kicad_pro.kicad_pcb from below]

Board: 2 copper layers, 291.8 x 134.6 mm, 367 parts (295 on the bottom side), 206 nets.

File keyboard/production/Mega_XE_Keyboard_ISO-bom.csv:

Designator,Footprint,Quantity,Value,LCSC Part #
"C1, C10, C11, C12, C13, C14, C15, C16, C17, C18, C19, C2, C20, C21, C22, C23, C24, C25, C26, C27, C28, C29, C3, C30, C31, C32, C33, C34, C35, C36, C37, C38, C39, C4, C40, C41, C42, C43, C44, C45, C46, C47, C48, C49, C5, C50, C51, C52, C53, C54, C55, C56, C57, C58, C59, C6, C60, C61, C62, C63, C64, C65, C66, C67, C68, C69, C7, C70, C71, C72, C73, C74, C75, C76, C77, C8, C84, C86, C87, C89, C9, C90, C91, C93, C95, C96, C97, C98",0402,88,100nF,C1525
"C100, C88, C92, C99",0402,4,100nF,
C78,0402,1,10uF,
"C79, C80, C81",0402,3,10uF,C15525
"C82, C83",0402,2,15pF,C1548
"C85, C94",0402,2,1uF,C52923
"D1, D101, D103, D105, D107, D109, D11, D111, D113, D115, D117, D119, D121, D123, D125, D127, D129, D13, D131, D144, D146, D148, D15, D150, D152, D17, D19, D21, D23, D25, D27, D29, D3, D31, D33, D35, D37, D39, D41, D43, D45, D47, D49, D5, D51, D53, D55, D57, D59, D61, D63, D65, D67, D69, D7, D71, D73, D75, D77, D79, D81, D83, D85, D87, D89, D9, D91, D93, D95, D97, D99",D_SOD-123,71,1N4148W,C81598
"D133, D134, D135, D136, D137, D138, D139, D140, D141, D142, D143",LED_SK6812MINI-E_3.2x2.8mm_P1.5mm_ReverseMount,11,SK6812MINI,C5378731
D154,LED_SK6812MINI-E_3.2x2.8mm_P1.5mm_ReverseMount,1,SK6812MINI,
J1,USB_C_Receptacle_C2765186,1,USB_C_Receptacle_USB2.0_16P,C2765186
"R3, R4",0402,2,5k1,C25905
"R5, R6, R9",0402,3,1k,C11702
"R7, R8",0402,2,27,C138021
"SW11, SW12, SW13, SW14, SW15, SW16, SW17, SW18, SW19, SW2, SW20, SW21, SW22, SW23, SW24, SW25, SW26, SW27, SW28, SW29, SW3, SW30, SW31, SW32, SW33, SW34, SW35, SW36, SW37, SW38, SW39, SW4, SW40, SW41, SW42, SW43, SW44, SW45, SW46, SW47, SW48, SW49, SW5, SW50, SW51, SW52, SW53, SW54, SW57, SW58, SW59, SW6, SW60, SW63, SW64, SW65, SW66, SW67, SW7, SW70, SW71, SW72, SW73, SW74, SW8, SW9",Kailh_socket_MX_1-00U,66,MX,C41430893
SW62,Kailh_socket_MX_1-00U,1,MX,C5156480
SW68,TactileSwitch,1,SW_BOOT_SELECT,C720477
SW69,TactileSwitch,1,SW_RESET,C720477
U1,SOIC-8_5.3x5.3mm_P1.27mm,1,W25Q128JVS,C97521
U2,SOT-223-3_TabPin2,1,NCP1117-3.3,C6186
U3,QFN-56-1EP_7x7mm_P0.4mm_EP3.2x3.2mm,1,RP2040,C2040
X1,Crystal_SMD_Abracon_ABM8AIG-4Pin_3.2x2.5mm,1,12MHz,C9002

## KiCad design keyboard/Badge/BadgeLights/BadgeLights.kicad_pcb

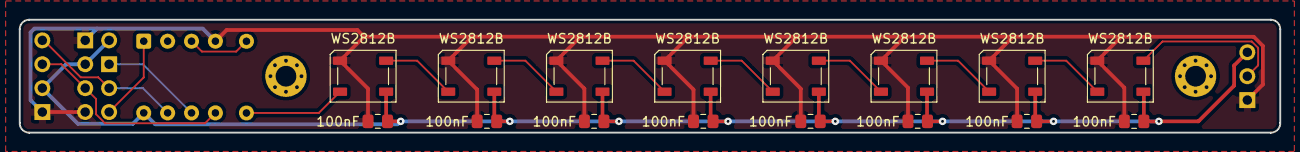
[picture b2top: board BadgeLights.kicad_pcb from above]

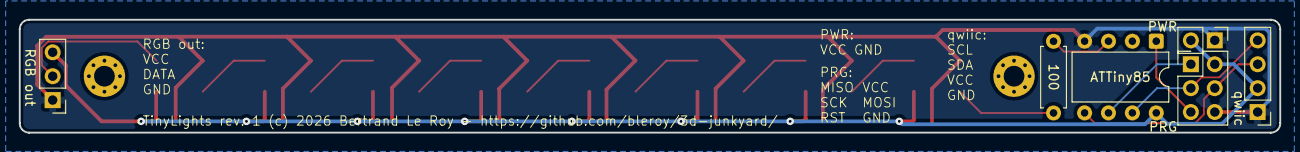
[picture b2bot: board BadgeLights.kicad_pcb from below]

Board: 2 copper layers, 134.0 x 12.0 mm, 24 parts (6 on the bottom side), 16 nets.

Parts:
C24, C25, C26, C27, C28, C29, C30, C31: 100nF; C_0805_2012Metric_Pad1.18x1.45mm_HandSolder
D1, D2, D3, D4, D5, D6, D7, D8: WS2812B; LED_WS2812B_PLCC4_5.0x5.0mm_P3.2mm
H1, H2: MountingHole_Pad; MountingHole_2.2mm_M2_Pad_Via
PRG: Conn_02x03_Odd_Even; PinHeader_2x03_P2.54mm_Vertical
PWR: Conn_01x02_Pin; PinHeader_1x02_P2.54mm_Vertical
R1: R; R_Axial_DIN0207_L6.3mm_D2.5mm_P7.62mm_Horizontal
RGB out: Conn_01x03_Pin; PinHeader_1x03_P2.54mm_Vertical
U1: ATtiny85-20P; DIP-8_W7.62mm
qwiic: Conn_01x04; PinHeader_1x04_P2.54mm_Vertical

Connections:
+5V: C24.1, C25.1, C26.1, C27.1, C28.1, C29.1, C30.1, C31.1, D1.1 (VDD), D2.1 (VDD), D3.1 (VDD), D4.1 (VDD), D5.1 (VDD), D6.1 (VDD), D7.1 (VDD), D8.1 (VDD), PRG.2, PWR.2, RGB out.3, U1.8 (VCC), qwiic.2
GND: C24.2, C25.2, C26.2, C27.2, C28.2, C29.2, C30.2, C31.2, D1.3 (VSS), D2.3 (VSS), D3.3 (VSS), D4.3 (VSS), D5.3 (VSS), D6.3 (VSS), D7.3 (VSS), D8.3 (VSS), PRG.6, PWR.1, RGB out.1, U1.4 (GND), qwiic.1
unnamed: D1.4 (DIN), R1.2
unnamed: D1.2 (DOUT), D2.4 (DIN)
unnamed: D2.2 (DOUT), D3.4 (DIN)
unnamed: D3.2 (DOUT), D4.4 (DIN)
unnamed: D4.2 (DOUT), D5.4 (DIN)
unnamed: D5.2 (DOUT), D6.4 (DIN)
unnamed: D6.2 (DOUT), D7.4 (DIN)
unnamed: D7.2 (DOUT), D8.4 (DIN)
unnamed: D8.2 (DOUT), RGB out.2
unnamed: PRG.1, U1.6 (PB1)
unnamed: PRG.3, U1.7 (PB2), qwiic.4
unnamed: PRG.4, U1.5 (AREF/PB0), qwiic.3
unnamed: PRG.5, U1.1 (~RESET/PB5)
unnamed: R1.1, U1.3 (XTAL2/PB4)

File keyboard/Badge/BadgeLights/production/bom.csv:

Designator,Footprint,Quantity,Value,LCSC Part #
"C24, C25, C26, C27, C28, C29, C30, C31",0805,8,100nF,
"D1, D2, D3, D4, D5, D6, D7, D8",LED_WS2812B_PLCC4_5.0x5.0mm_P3.2mm,8,WS2812B,
PRG,PinHeader_2x03_P2.54mm_Vertical,1,Conn_02x03_Odd_Even,
PWR,PinHeader_1x02_P2.54mm_Vertical,1,Conn_01x02_Pin,
QWIIC,PinHeader_1x04_P2.54mm_Vertical,1,Conn_01x04,
R1,R_Axial_DIN0207_L6.3mm_D2.5mm_P7.62mm_Horizontal,1,R,
RGB OUT,PinHeader_1x03_P2.54mm_Vertical,1,Conn_01x03_Pin,
U1,DIP-8_W7.62mm,1,ATtiny85-20P,

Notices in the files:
keyboard/Badge/BadgeLights/BadgeLights.kicad_pcb:
TinyLights rev. 1 (c) 2026 Bertrand Le Roy - https://github.com/bleroy/3d-junkyard
keyboard/MegaXE-keyboard-ISO.kicad_pro.kicad_pcb:
© Bertrand Le Roy 2026
